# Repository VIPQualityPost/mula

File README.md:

A small 16ch 100MHz logic analyzer with 2-5V protected inputs that is 
compliant with SUMP/OLS and is usable in sigrok. It is based on 
the rp2040 rust logic analyzer firmware 
[`ula`](https://github.com/dotcypress/ula.git) written by 
[@dotcypress](https://github.com/dotcypress). The 
small form factor is designed for a socket to be designed into a circuit board 
using cheap and widely available m.2 sockets, or by using some custom 
carriers which allow you to use popular flying probes, like the ones 
provided with bitmagic or the classic HP 01652-61608.

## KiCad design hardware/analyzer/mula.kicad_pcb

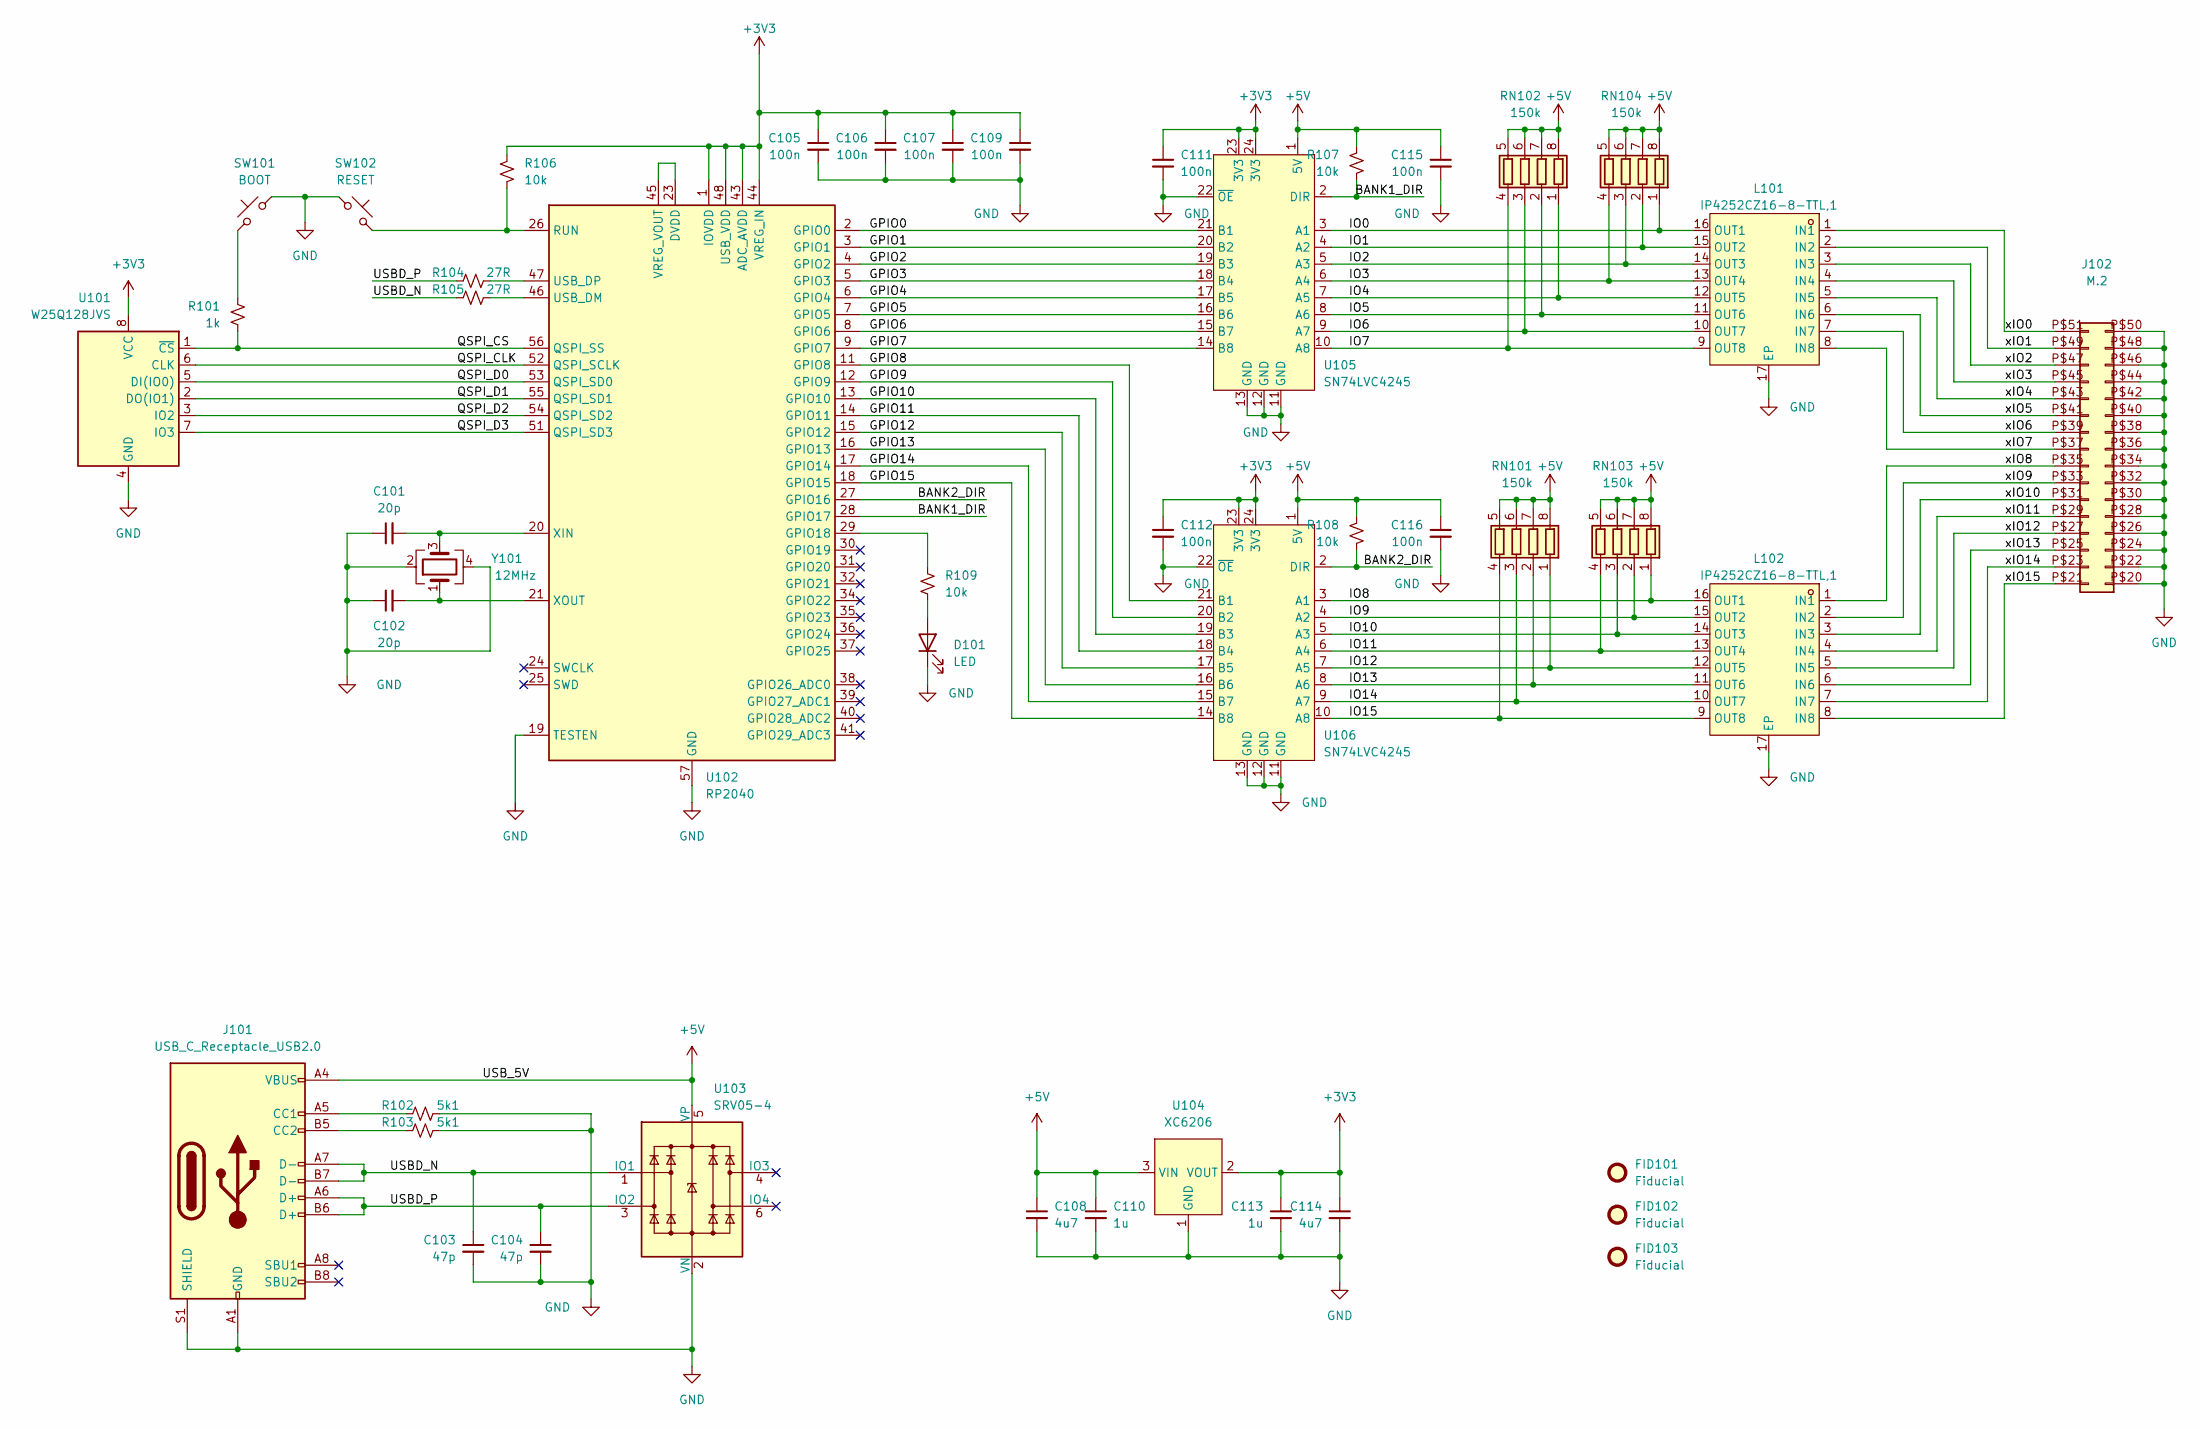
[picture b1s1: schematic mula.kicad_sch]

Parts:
C101, C102: 20p; C_0402_1005Metric
C103, C104: 47p; C_0402_1005Metric
C105, C106, C107, C109, C111, C112, C115, C116: 100n; C_0402_1005Metric
C108, C114: 4u7; C_0402_1005Metric
C110, C113: 1u; C_0402_1005Metric
D101: LED; D_0603_1608Metric
FID101, FID102, FID103: Fiducial; Fiducial_0.5mm_Mask1mm
J101: USB_C_Receptacle_USB2.0; USB_C_Receptacle_HRO_TYPE-C-31-M-12; LCSC Part C165948
J102: M.2; M.2-B-KEY
L101, L102: IP4252CZ16-8-TTL,1; UDFN-16_L3.3-W1.4-P0.40-BL-EP; LCSC Part C458218
R101: 1k; R_0402_1005Metric
R102, R103: 5k1; R_0402_1005Metric
R104, R105: 27R; R_0402_1005Metric
R106, R107, R108, R109: 10k; R_0402_1005Metric
RN101, RN102, RN103, RN104: 150k; R_Array_Concave_4x0402; LCSC Part C425271
SW101: BOOT; TS-1187A-B-A-B; LCSC Part C318884
SW102: RESET; TS-1187A-B-A-B; LCSC Part C318884
U101: W25Q128JVS; SOIC-8W_5.3x5.3mm_P1.27mm; LCSC Part C97521
U102: RP2040; QFN-56-1EP_7x7mm_P0.4mm_EP3.2x3.2mm; LCSC Part C2040
U103: SRV05-4; SOT-23-6; LCSC Part C85364
U104: XC6206; SOT-23; LCSC Part C5446
U105, U106: SN74LVC4245; TSSOP-24_4.4x7.8mm_P0.65mm; LCSC Part C7859
Y101: 12MHz; Crystal_SMD_3225-4Pin_3.2x2.5mm; LCSC Part C9002

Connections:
+3V3: C105.1, C106.1, C107.1, C109.1, C111.1, C112.1, C113.1, C114.1, R106.1, U101.8 (VCC), U102.1 (IOVDD), U102.10 (IOVDD), U102.22 (IOVDD), U102.33 (IOVDD), U102.42 (IOVDD), U102.43 (ADC_AVDD), U102.44 (VREG_IN), U102.48 (USB_VDD), U102.49 (IOVDD), U104.2 (VOUT), U105.23 (3V3), U105.24 (3V3), U106.23 (3V3), U106.24 (3V3)
+5V: C108.1, C110.1, C115.1, C116.1, J101.A4 (VBUS), J101.A9 (VBUS), J101.B4 (VBUS), J101.B9 (VBUS), R107.1, R108.1, RN101.5 (R4.2), RN101.6 (R3.2), RN101.7 (R2.2), RN101.8 (R1.2), RN102.5 (R4.2), RN102.6 (R3.2), RN102.7 (R2.2), RN102.8 (R1.2), RN103.5 (R4.2), RN103.6 (R3.2), RN103.7 (R2.2), RN103.8 (R1.2), RN104.5 (R4.2), RN104.6 (R3.2), RN104.7 (R2.2), RN104.8 (R1.2), U103.5 (VP), U104.3 (VIN), U105.1 (5V), U106.1 (5V)
/BANK1_DIR: R107.2, U102.28 (GPIO17), U105.2 (DIR)
/BANK2_DIR: R108.2, U102.27 (GPIO16), U106.2 (DIR)
/GPIO0: U102.2 (GPIO0), U105.21 (B1)
/GPIO1: U102.3 (GPIO1), U105.20 (B2)
/GPIO2: U102.4 (GPIO2), U105.19 (B3)
/GPIO3: U102.5 (GPIO3), U105.18 (B4)
/GPIO4: U102.6 (GPIO4), U105.17 (B5)
/GPIO5: U102.7 (GPIO5), U105.16 (B6)
/GPIO6: U102.8 (GPIO6), U105.15 (B7)
/GPIO7: U102.9 (GPIO7), U105.14 (B8)
/GPIO8: U102.11 (GPIO8), U106.21 (B1)
/GPIO9: U102.12 (GPIO9), U106.20 (B2)
/GPIO10: U102.13 (GPIO10), U106.19 (B3)
/GPIO11: U102.14 (GPIO11), U106.18 (B4)
/GPIO12: U102.15 (GPIO12), U106.17 (B5)
/GPIO13: U102.16 (GPIO13), U106.16 (B6)
/GPIO14: U102.17 (GPIO14), U106.15 (B7)
/GPIO15: U102.18 (GPIO15), U106.14 (B8)
/IO0: L101.16 (OUT1), RN104.1 (R1.1), U105.3 (A1)
/IO1: L101.15 (OUT2), RN104.2 (R2.1), U105.4 (A2)
/IO2: L101.14 (OUT3), RN104.3 (R3.1), U105.5 (A3)
/IO3: L101.13 (OUT4), RN104.4 (R4.1), U105.6 (A4)
/IO4: L101.12 (OUT5), RN102.1 (R1.1), U105.7 (A5)
/IO5: L101.11 (OUT6), RN102.2 (R2.1), U105.8 (A6)
/IO6: L101.10 (OUT7), RN102.3 (R3.1), U105.9 (A7)
/IO7: L101.9 (OUT8), RN102.4 (R4.1), U105.10 (A8)
/IO8: L102.16 (OUT1), RN103.1 (R1.1), U106.3 (A1)
/IO9: L102.15 (OUT2), RN103.2 (R2.1), U106.4 (A2)
/IO10: L102.14 (OUT3), RN103.3 (R3.1), U106.5 (A3)
/IO11: L102.13 (OUT4), RN103.4 (R4.1), U106.6 (A4)
/IO12: L102.12 (OUT5), RN101.1 (R1.1), U106.7 (A5)
/IO13: L102.11 (OUT6), RN101.2 (R2.1), U106.8 (A6)
/IO14: L102.10 (OUT7), RN101.3 (R3.1), U106.9 (A7)
/IO15: L102.9 (OUT8), RN101.4 (R4.1), U106.10 (A8)
/QSPI_CLK: U101.6 (CLK), U102.52 (QSPI_SCLK)
/QSPI_CS: R101.2, U101.1 (~CS), U102.56 (QSPI_SS)
/QSPI_D0: U101.5 (DI(IO0)), U102.53 (QSPI_SD0)
/QSPI_D1: U101.2 (DO(IO1)), U102.55 (QSPI_SD1)
/QSPI_D2: U101.3 (IO2), U102.54 (QSPI_SD2)
/QSPI_D3: U101.7 (IO3), U102.51 (QSPI_SD3)
/USBD_N: C103.1, J101.A7 (D-), J101.B7 (D-), R105.1, U103.1 (IO1)
/USBD_P: C104.1, J101.A6 (D+), J101.B6 (D+), R104.1, U103.3 (IO2)
/xIO0: J102.P$51 (Pin_32), L101.1 (IN1)
/xIO1: J102.P$49 (Pin_31), L101.2 (IN2)
/xIO2: J102.P$47 (Pin_30), L101.3 (IN3)
/xIO3: J102.P$45 (Pin_29), L101.4 (IN4)
/xIO4: J102.P$43 (Pin_28), L101.5 (IN5)
/xIO5: J102.P$41 (Pin_27), L101.6 (IN6)
/xIO6: J102.P$39 (Pin_26), L101.7 (IN7)
/xIO7: J102.P$37 (Pin_25), L101.8 (IN8)
/xIO8: J102.P$35 (Pin_24), L102.1 (IN1)
/xIO9: J102.P$33 (Pin_23), L102.2 (IN2)
/xIO10: J102.P$31 (Pin_22), L102.3 (IN3)
/xIO11: J102.P$29 (Pin_21), L102.4 (IN4)
/xIO12: J102.P$27 (Pin_20), L102.5 (IN5)
/xIO13: J102.P$25 (Pin_19), L102.6 (IN6)
/xIO14: J102.P$23 (Pin_18), L102.7 (IN7)
/xIO15: J102.P$21 (Pin_17), L102.8 (IN8)
GND: C101.1, C102.1, C103.2, C104.2, C105.2, C106.2, C107.2, C108.2, C109.2, C110.2, C111.2, C112.2, C113.2, C114.2, C115.2, C116.2, D101.1 (K), J101.A1 (GND), J101.A12 (GND), J101.B1 (GND), J101.B12 (GND), J101.S1 (SHIELD), J102.P$20 (Pin_1), J102.P$22 (Pin_2), J102.P$24 (Pin_3), J102.P$26 (Pin_4), J102.P$28 (Pin_5), J102.P$30 (Pin_6), J102.P$32 (Pin_7), J102.P$34 (Pin_8), J102.P$36 (Pin_9), J102.P$38 (Pin_10), J102.P$40 (Pin_11), J102.P$42 (Pin_12), J102.P$44 (Pin_13), J102.P$46 (Pin_14), J102.P$48 (Pin_15), J102.P$50 (Pin_16), L101.17 (EP), L102.17 (EP), R102.2, R103.2, SW101.1, SW102.1, U101.4 (GND), U102.19 (TESTEN), U102.57 (GND), U103.2 (VN), U104.1 (GND), U105.11 (GND), U105.12 (GND), U105.13 (GND), U105.22 (~OE), U106.11 (GND), U106.12 (GND), U106.13 (GND), U106.22 (~OE), Y101.2, Y101.4
unnamed: D101.2 (A), R109.2
unnamed: J101.A5 (CC1), R102.1
unnamed: J101.B5 (CC2), R103.1
unnamed: R101.1, SW101.2
unnamed: R109.1, U102.29 (GPIO18)
unnamed: R106.2, SW102.2, U102.26 (RUN)
unnamed: R105.2, U102.46 (USB_DM)
unnamed: R104.2, U102.47 (USB_DP)
unnamed: U102.23 (DVDD), U102.45 (VREG_VOUT), U102.50 (DVDD)
unnamed: C101.2, U102.20 (XIN), Y101.3
unnamed: C102.2, U102.21 (XOUT), Y101.1

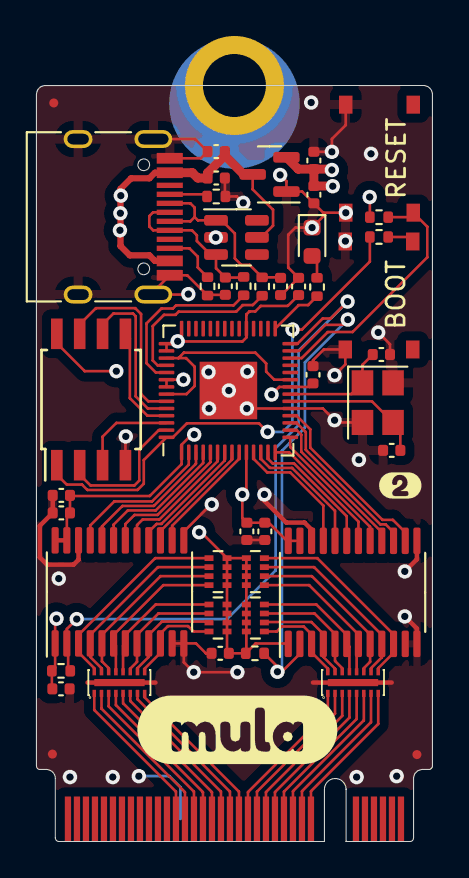
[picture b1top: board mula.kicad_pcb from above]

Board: 4 copper layers, 22.0 x 42.0 mm, 48 parts (0 on the bottom side), 72 nets.

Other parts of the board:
kibuzzard-64C5EFF0: G***; kibuzzard-64C5EFF0
kibuzzard-64C8408B: G***; kibuzzard-64C8408B

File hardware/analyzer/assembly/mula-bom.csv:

Comment,Designator,Footprint,JLCPCB Part #
10k,"R109,R107,R108,R106",0402_R,
LED,D101,0603_D,C2290
"IP4252CZ16-8-TTL,1","L102,L101",UDFN-16,C458218
W25Q128JVS,U101,SOIC-8,C97521
12MHz,Y101,Crystal_SMD_3225,C9002
SN74LVC4245,"U106,U105",TSSOP-24,C7859
XC6206,U104,SOT-23,C5446
SRV05-4,U103,SOT-23-6,C85364
RP2040,U102,QFN-56,C2040
BUTTON,"SW101, SW102",TS-1187A-B-A-B,C318884
150k,"RN104,RN103,RN102,RN101",R_Array_Concave_4x0402,C425271
27R,"R105,R104",0402_R,
5k1,"R103,R102",0402_R,
1k,R101,0402_R,
USB_C_Receptacle_USB2.0,J101,HRO_TYPE-C-31-M-12,C165948
100n,"C116,C115,C112,C111,C109,C107,C106,C105",0402_C,
4u7,"C114,C108",0402_C,
1u,"C113,C110",0402_C,
47p,"C104,C103",0402_C,
20p,"C102,C101",0402_C,

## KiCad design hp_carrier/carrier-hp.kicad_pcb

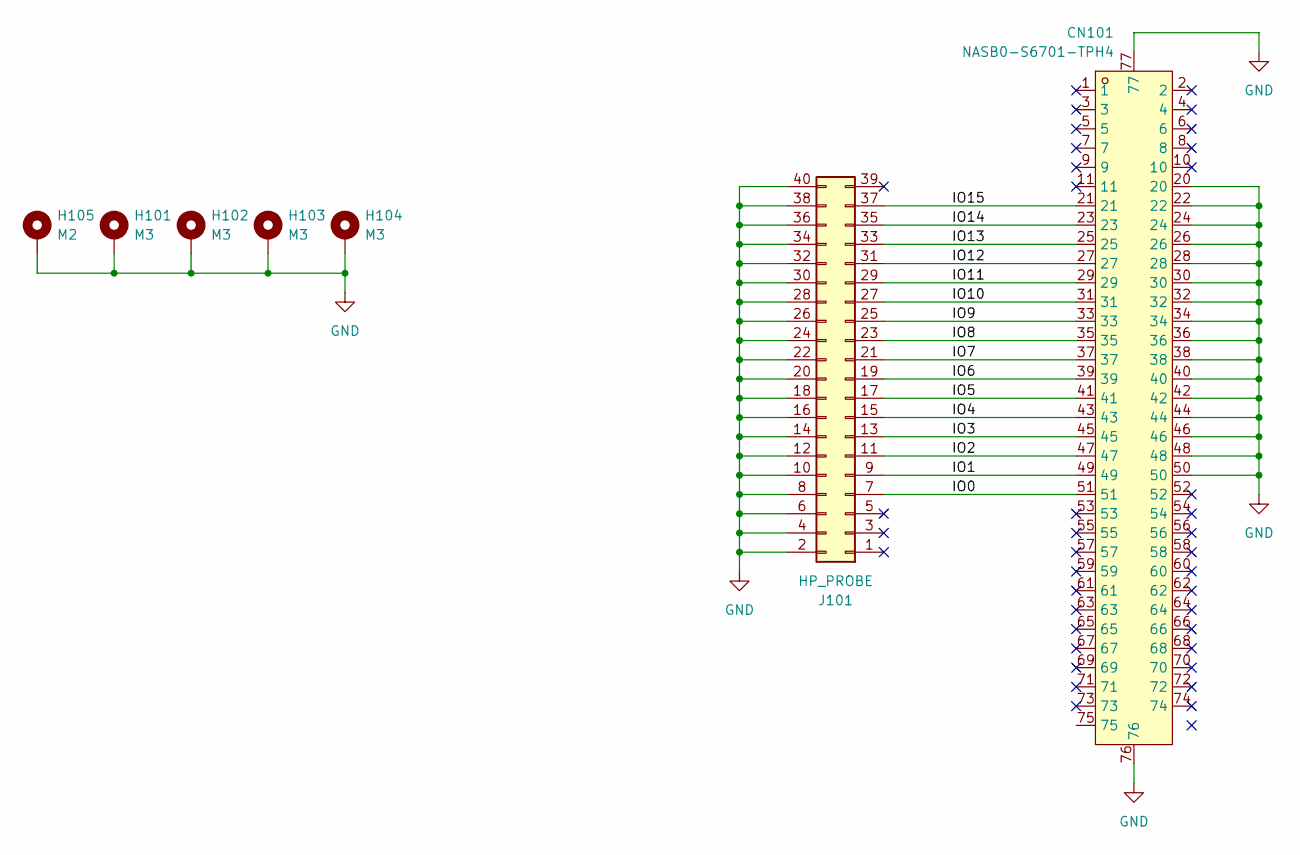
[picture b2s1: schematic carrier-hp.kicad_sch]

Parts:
CN101: NASB0-S6701-TPH4; CONN-SMD_NXSB0-S67XX-XXH4; LCSC Part C367030
H101, H102, H103, H104: M3; MountingHole_3mm_Pad
H105: M2; MountingHole_2.2mm_M2_DIN965_Pad
J101: HP_PROBE; IDC-Header_2x20_P2.54mm_Latch_Horizontal

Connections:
/IO0: CN101.51, J101.7
/IO1: CN101.49, J101.9
/IO2: CN101.47, J101.11
/IO3: CN101.45, J101.13
/IO4: CN101.43, J101.15
/IO5: CN101.41, J101.17
/IO6: CN101.39, J101.19
/IO7: CN101.37, J101.21
/IO8: CN101.35, J101.23
/IO9: CN101.33, J101.25
/IO10: CN101.31, J101.27
/IO11: CN101.29, J101.29
/IO12: CN101.27, J101.31
/IO13: CN101.25, J101.33
/IO14: CN101.23, J101.35
/IO15: CN101.21, J101.37
GND: CN101.20, CN101.22, CN101.24, CN101.26, CN101.28, CN101.30, CN101.32, CN101.34, CN101.36, CN101.38, CN101.40, CN101.42, CN101.44, CN101.46, CN101.48, CN101.50, CN101.76, CN101.77, H101.1, H102.1, H103.1, H104.1, H105.1, J101.2, J101.4, J101.6, J101.8, J101.10, J101.12, J101.14, J101.16, J101.18, J101.20, J101.22, J101.24, J101.26, J101.28, J101.30, J101.32, J101.34, J101.36, J101.38, J101.40

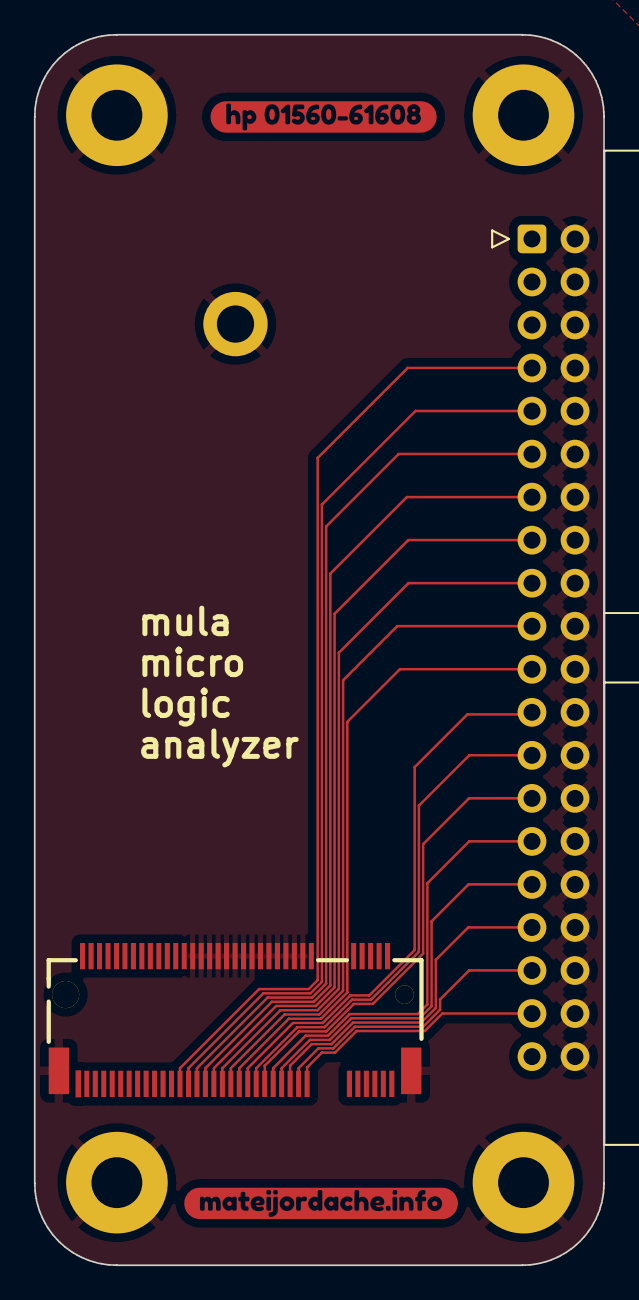
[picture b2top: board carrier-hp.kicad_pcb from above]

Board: 4 copper layers, 33.6 x 72.6 mm, 9 parts (0 on the bottom side), 17 nets.

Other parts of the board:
kibuzzard-64C862C8: G***; kibuzzard-64C862C8
kibuzzard-64C85072: G***; kibuzzard-64C85072

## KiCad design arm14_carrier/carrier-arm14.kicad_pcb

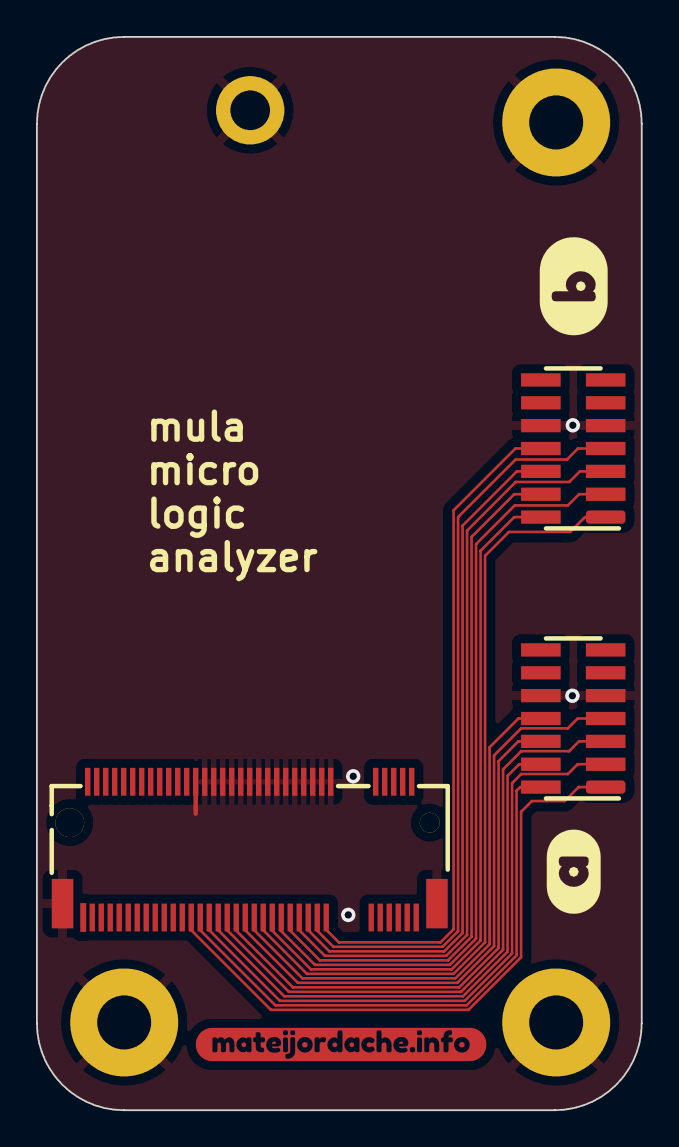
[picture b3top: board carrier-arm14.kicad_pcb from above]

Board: 4 copper layers, 33.6 x 59.6 mm, 10 parts (0 on the bottom side), 17 nets.

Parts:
CN101: NASB0-S6701-TPH4; CONN-SMD_NXSB0-S67XX-XXH4
H102, H103, H104: M3; MountingHole_3mm_Pad
H105: M2; MountingHole_2.2mm_M2_DIN965_Pad
J101: BANK_A; HDR-SMD_14P-P1.27-V-M-R2-C7-LS5.3
J102: BANK_B; HDR-SMD_14P-P1.27-V-M-R2-C7-LS5.3
kibuzzard-64C6FCDD: G***; kibuzzard-64C6FCDD
kibuzzard-64C70043: G***; kibuzzard-64C70043
kibuzzard-64C85072: G***; kibuzzard-64C85072

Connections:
/IO0: CN101.51, J101.1
/IO1: CN101.49, J101.2
/IO2: CN101.47, J101.3
/IO3: CN101.45, J101.4
/IO4: CN101.43, J101.5
/IO5: CN101.41, J101.6
/IO6: CN101.39, J101.7
/IO7: CN101.37, J101.8
/IO8: CN101.35, J102.1
/IO9: CN101.33, J102.2
/IO10: CN101.31, J102.3
/IO11: CN101.29, J102.4
/IO12: CN101.27, J102.5
/IO13: CN101.25, J102.6
/IO14: CN101.23, J102.7
/IO15: CN101.21, J102.8
GND: CN101.20, CN101.22, CN101.24, CN101.26, CN101.28, CN101.30, CN101.32, CN101.34, CN101.36, CN101.38, CN101.40, CN101.42, CN101.44, CN101.46, CN101.48, CN101.50, CN101.76, CN101.77, H102.1, H103.1, H104.1, H105.1, J101.9, J101.10, J102.9, J102.10

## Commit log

2023-08-01 init commit
2023-08-01 add readme
2023-08-01 restructure
2023-08-06 move things around
2023-08-23 add in assembly files
2023-08-23 remove extra cpl pos file
